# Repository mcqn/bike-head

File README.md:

# Bike Head

Making your bike more fun (if that's possible) by giving it a head.

A laser-cut template to make a cardboard head to mount on the handlebars of your bike.  Then customize it with craft supplies or LEDs and a Microbit.

## Notes on creating the design

In FreeCAD...

1. Created a sketch of the side profile
1. Made a copy of that sketch
1. Opened the attachment editor for each sketch and offset one by 75mm on Z and -8&deg; rotation around Y, and the other by -75 and 8&deg;
1. Then in the Surface workbench, filled in each side to give two surfaces
1. And then repeatedly used the boundary curve to create each connecting surface between the sides
1. In the Draft workbench I selected all the centre, connecting surfaces and upgraded them to a shell
1. Then in the Mesh workbench I could convert the shell to a mesh and then unwrap it to get the net for those shapes
1. The convert to mesh and unwrap process was repeated for the two sides
1. Then used Transform to orient the sides to broadly the right place
1. And in the Draft workbench rotated and moved the sides to be offset by 3mm from the long face
   1. Selected each end of the corresponding lines in the side and the centre piece which are to be lined up, and noted their `x` and `y` coordinates.
   1. Worked out the angle of the centre piece line with respect to `y` (in this instance) - `theta`, with `tan^-1(x_diff/y_diff)`
   1. Worked out new coordinates for corresponding point in the side with `x_offset` being `3 * sin(90-theta)` and `y_offset` being `3* cos(90-theta)`
   1. Work out the distance to move the side so it ends up at the right place.  Use the Placement in the side's properties to nudge it
   1. Rotate the side to line up parallel to the corresponding line in the centre.  I ended up eyeballing this rather than calculating it
   1. Repeat for the other side

## Game Notes

### Pacman

### Tick

1. Start up and loop until someone is chosen or a timeout happens:
   1. Transmit your ID
   1. Wait to receive someone-else's ID
   1. Vote on who should be `it`?
1. If it was a timeout, assume someone else is `it` and proceed

1. To begin with, use a button press to select someone as `it`
1. Loop:
   1. If I'm `it`:
      1. Light LED
      1. Broadcast our ID
      1. Listen for a broadcast
      1. If a request to be `it` is received, send a confirmation of passing on
   1. If not `it`:
      1. Turn off LED
      1. Listen for a broadcast
      1. If one found, reply with a request to be `it`
      1. If it's a confirmation of `it`, you're `it`, count down from 5 before looping round

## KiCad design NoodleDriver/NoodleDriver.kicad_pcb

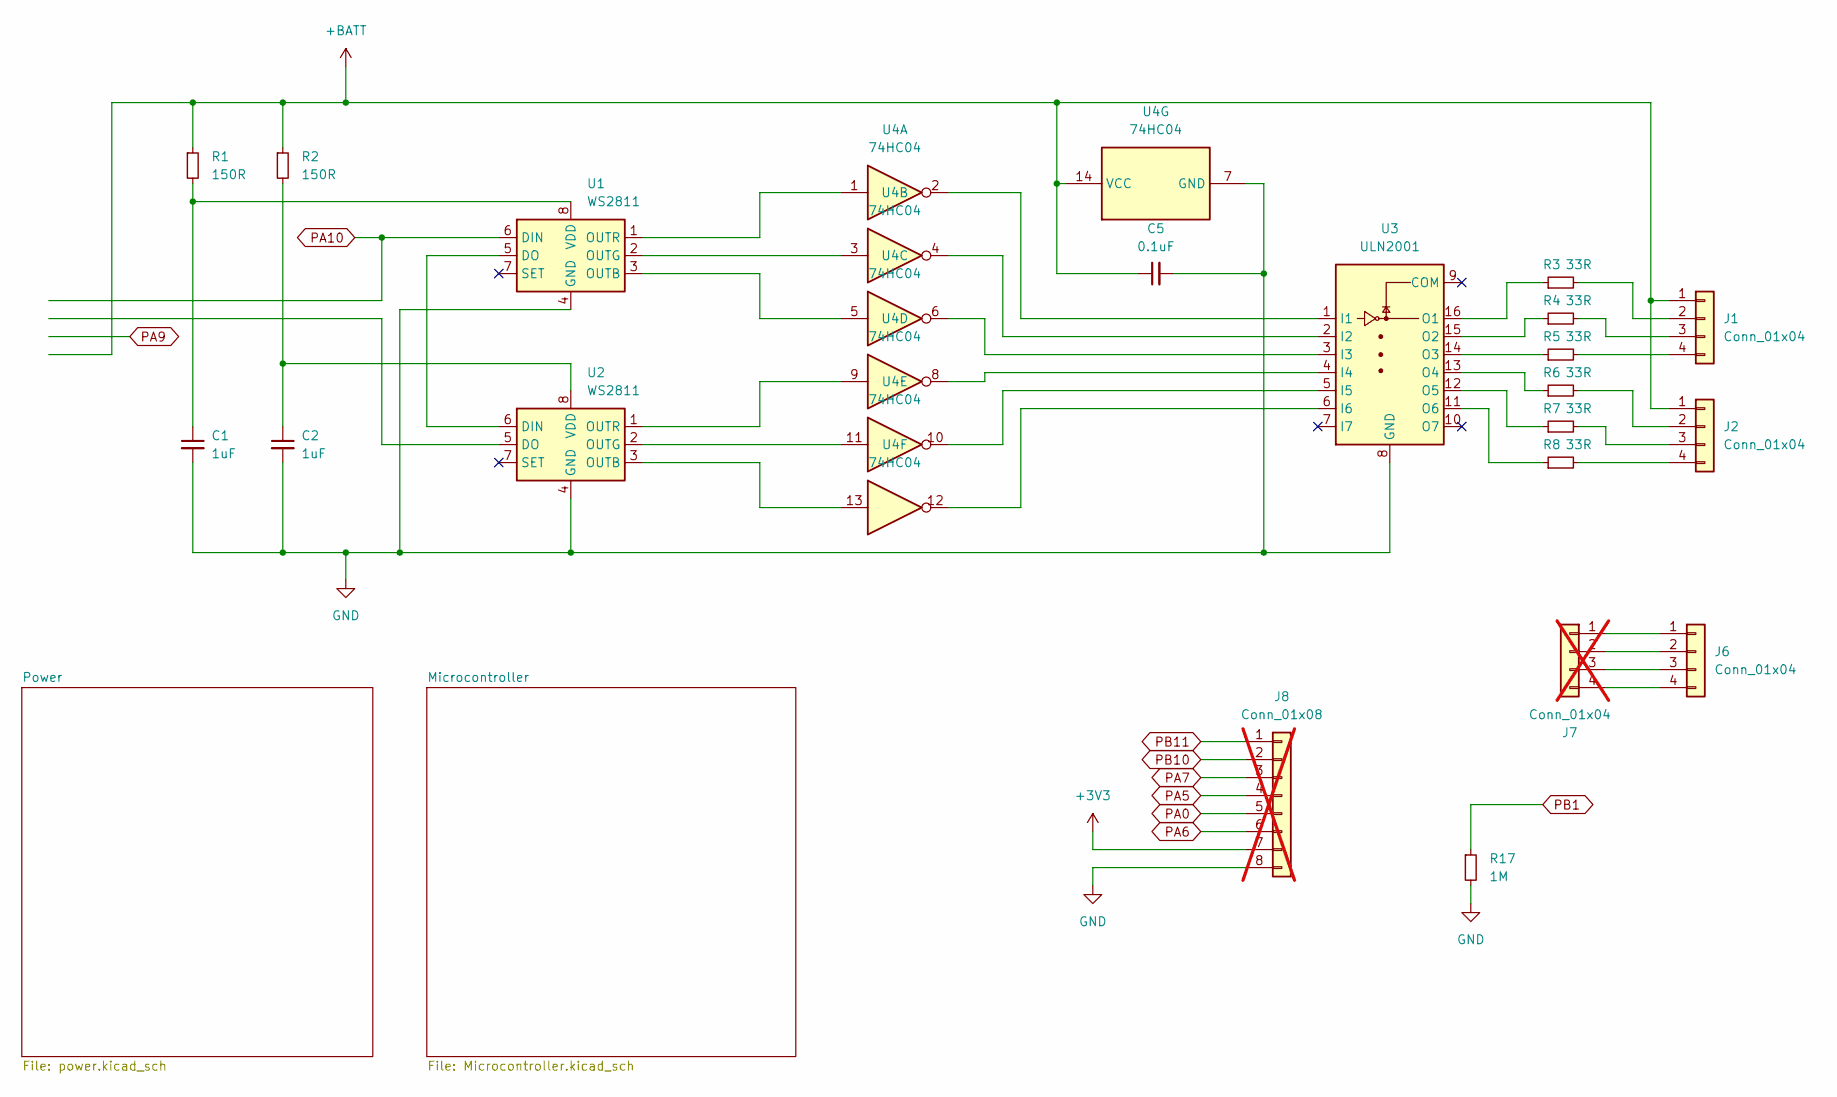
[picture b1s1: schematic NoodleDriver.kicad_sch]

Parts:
C1, C2: 1uF; C_0402_1005Metric; LCSC C14445
C5: 0.1uF; C_0402_1005Metric; LCSC C77020
J1, J2, J6: Conn_01x04; MagneticPogoPinConnector_1x04_P2.54mm_Horizontal
J7: Conn_01x04; PinSocket_1x04_P2.54mm_Vertical; not fitted
J8: Conn_01x08; PinSocket_1x08_P2.54mm_Vertical; not fitted
R1, R2: 150R; R_0402_1005Metric; LCSC C138054
R3, R4, R5, R6, R7, R8: 33R; R_0603_1608Metric
R17: 1M; R_0402_1005Metric
U1, U2: WS2811; SOP-8_3.76x4.96mm_P1.27mm; LCSC C114581
U3: ULN2001; SOIC-16_3.9x9.9mm_P1.27mm; LCSC C165966
U4: 74HC04; SOIC-14_3.9x8.7mm_P1.27mm; LCSC C86613

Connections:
+3V3: J8.7; also elsewhere on the board
+BATT: C5.1, J1.1, J2.1, R1.1, R2.1, U4.14 (VCC); also elsewhere on the board
GND: C1.2, C2.2, C5.2, J8.8, R17.2, U1.4 (GND), U2.4 (GND), U3.8 (GND), U4.7 (GND); also elsewhere on the board
unnamed: J1.2, R3.2
unnamed: J1.3, R4.2
unnamed: J1.4, R5.2
unnamed: J2.2, R6.2
unnamed: J2.3, R7.2
unnamed: J2.4, R8.2
unnamed: J6.1, J7.1
unnamed: J6.2, J7.2
unnamed: J6.3, J7.3
unnamed: J6.4, J7.4
unnamed: U1.5 (DO), U2.6 (DIN)
unnamed: U1.3 (OUTB), U4.5
unnamed: U1.2 (OUTG), U4.3
unnamed: U1.1 (OUTR), U4.1
unnamed: C1.1, R1.2, U1.8 (VDD)
unnamed: U2.3 (OUTB), U4.13
unnamed: U2.2 (OUTG), U4.11
unnamed: U2.1 (OUTR), U4.9
unnamed: C2.1, R2.2, U2.8 (VDD)
unnamed: U3.1 (I1), U4.2
unnamed: U3.2 (I2), U4.4
unnamed: U3.3 (I3), U4.6
unnamed: U3.4 (I4), U4.8
unnamed: U3.5 (I5), U4.10
unnamed: U3.6 (I6), U4.12
unnamed: R3.1, U3.16 (O1)
unnamed: R4.1, U3.15 (O2)
unnamed: R5.1, U3.14 (O3)
unnamed: R6.1, U3.13 (O4)
unnamed: R7.1, U3.12 (O5)
unnamed: R8.1, U3.11 (O6)
PA0: J8.5; also elsewhere on the board
PA5: J8.4; also elsewhere on the board
PA6: J8.6; also elsewhere on the board
PA7: J8.3; also elsewhere on the board
PA10: U1.6 (DIN); also elsewhere on the board
PB1: R17.1; also elsewhere on the board
PB10: J8.2; also elsewhere on the board
PB11: J8.1; also elsewhere on the board

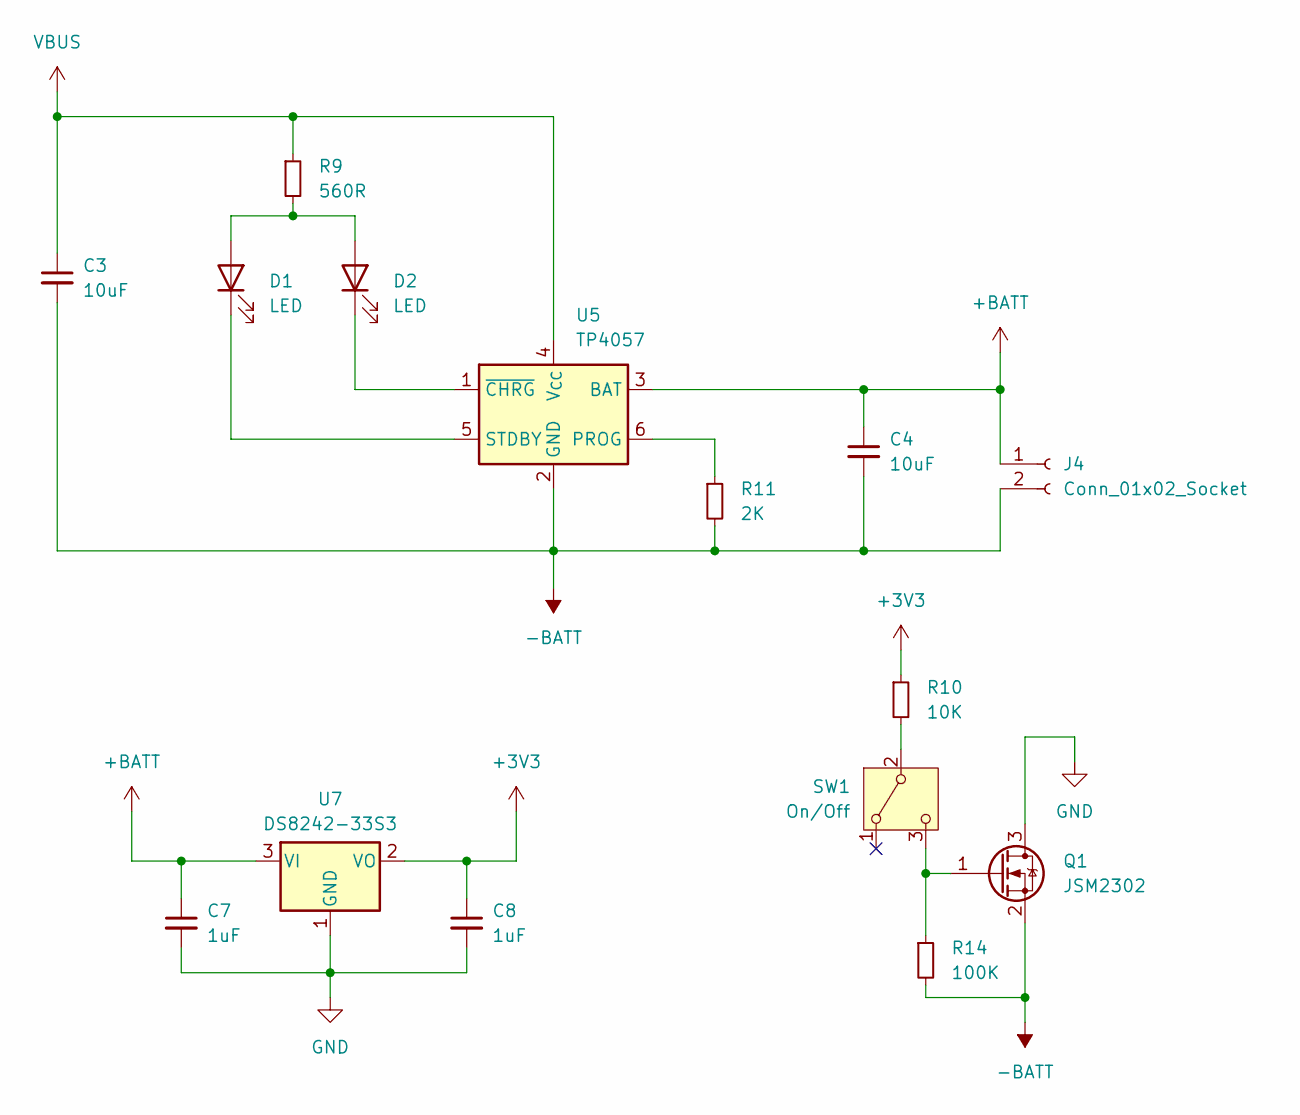
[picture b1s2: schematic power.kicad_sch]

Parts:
C3, C4: 10uF; C_0603_1608Metric; LCSC C6119842
C7, C8: 1uF; C_0402_1005Metric; LCSC C14445
D1, D2: LED; LED_0402_1005Metric
J4: Conn_01x02_Socket; JST_PH_B2B-PH-SM4-TB_1x02-1MP_P2.00mm_Vertical
Q1: JSM2302; SOT-23; LCSC C916403
R9: 560R; R_0402_1005Metric; LCSC C163460
R10: 10K; R_0402_1005Metric
R11: 2K; R_0402_1005Metric; LCSC C4109
R14: 100K; R_0402_1005Metric
SW1: On/Off; SW_Slide_SPDT_Angled_CK_OS102011MA1Q; Farnell 1201431
U5: TP4057; TSOT-23-6; LCSC C725791
U7: DS8242-33S3; SOT-23-3; LCSC C5884132

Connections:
+3V3: C8.1, R10.1, U7.2 (VO); also elsewhere on the board
+BATT: C4.1, C7.1, J4.1, U5.3 (BAT), U7.3 (VI); also elsewhere on the board
-BATT: C3.2, C4.2, J4.2, Q1.2 (S), R11.2, R14.2, U5.2 (GND); also elsewhere on the board
GND: C7.2, C8.2, Q1.3 (D), U7.1 (GND); also elsewhere on the board
unnamed: D1.2 (A), D2.2 (A), R9.2
unnamed: D1.1 (K), U5.5 (STDBY)
unnamed: D2.1 (K), U5.1 (~CHRG)
unnamed: Q1.1 (G), R14.1, SW1.3 (C)
unnamed: R10.2, SW1.2 (B)
unnamed: R11.1, U5.6 (PROG)
VBUS: C3.1, R9.1, U5.4 (V_{CC}); also elsewhere on the board

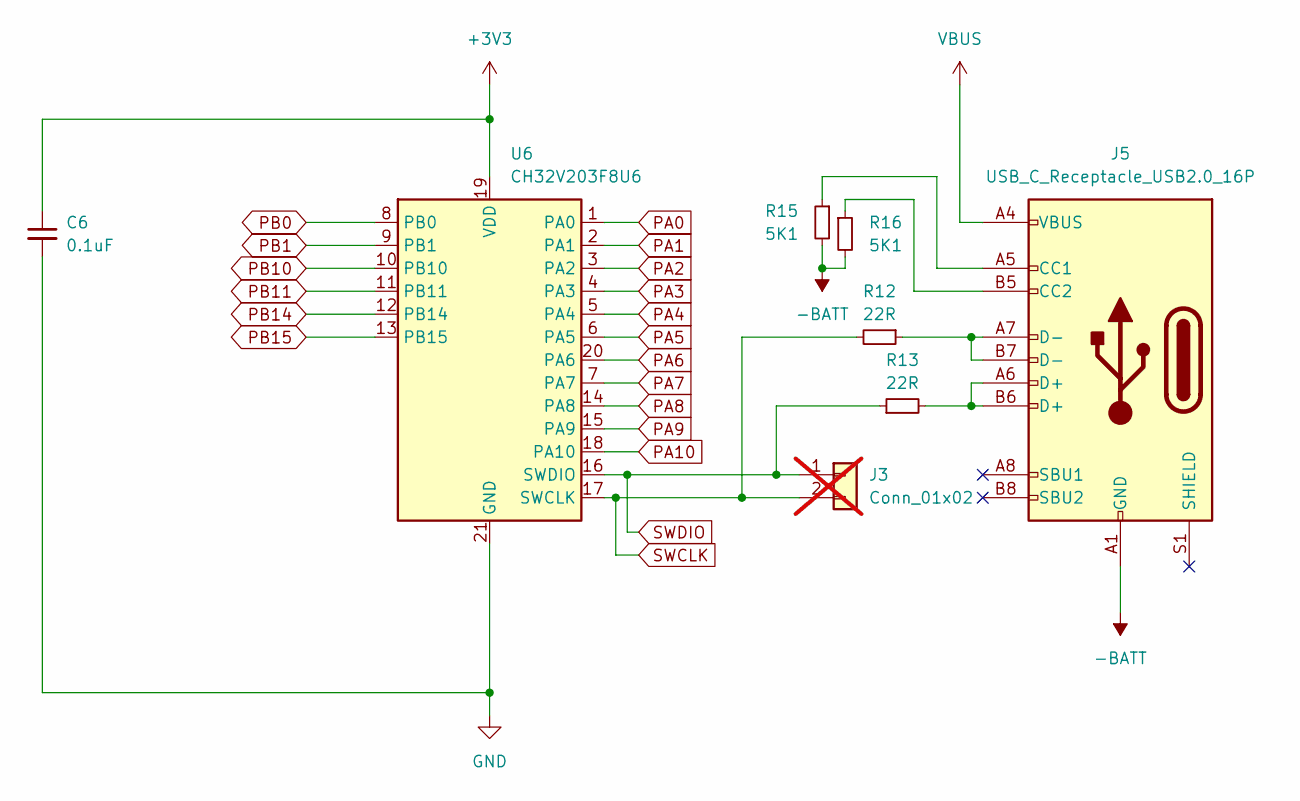
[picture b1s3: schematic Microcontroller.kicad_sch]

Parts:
C6: 0.1uF; C_0402_1005Metric; LCSC C77020
J3: Conn_01x02; PinSocket_1x02_P2.54mm_Vertical; not fitted
J5: USB_C_Receptacle_USB2.0_16P; USB_C_PADDLE
R12, R13: 22R; R_0402_1005Metric; LCSC C114765
R15, R16: 5K1; R_0402_1005Metric; LCSC C25905
U6: CH32V203F8U6; QFN-20-1EP_3x3mm_P0.45mm_EP1.6x1.6mm; LCSC C7570477

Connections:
+3V3: C6.1, U6.19 (VDD); also elsewhere on the board
-BATT: J5.A1 (GND), J5.A12 (GND), J5.B1 (GND), J5.B12 (GND), R15.2, R16.2; also elsewhere on the board
GND: C6.2, U6.21 (GND); also elsewhere on the board
unnamed: J5.A5 (CC1), R15.1
unnamed: J5.B5 (CC2), R16.1
unnamed: J5.A6 (D+), J5.B6 (D+), R13.2
unnamed: J5.A7 (D-), J5.B7 (D-), R12.1
PA0: U6.1 (PA0); also elsewhere on the board
PA1: U6.2 (PA1)
PA2: U6.3 (PA2)
PA3: U6.4 (PA3)
PA4: U6.5 (PA4)
PA5: U6.6 (PA5); also elsewhere on the board
PA6: U6.20 (PA6); also elsewhere on the board
PA7: U6.7 (PA7); also elsewhere on the board
PA8: U6.14 (PA8)
PA9: U6.15 (PA9)
PA10: U6.18 (PA10); also elsewhere on the board
PB0: U6.8 (PB0)
PB1: U6.9 (PB1); also elsewhere on the board
PB10: U6.10 (PB10); also elsewhere on the board
PB11: U6.11 (PB11); also elsewhere on the board
PB14: U6.12 (PB14)
PB15: U6.13 (PB15)
SWCLK: J3.2, R12.2, U6.17 (SWCLK)
SWDIO: J3.1, R13.1, U6.16 (SWDIO)
VBUS: J5.A4 (VBUS), J5.A9 (VBUS), J5.B4 (VBUS), J5.B9 (VBUS); also elsewhere on the board

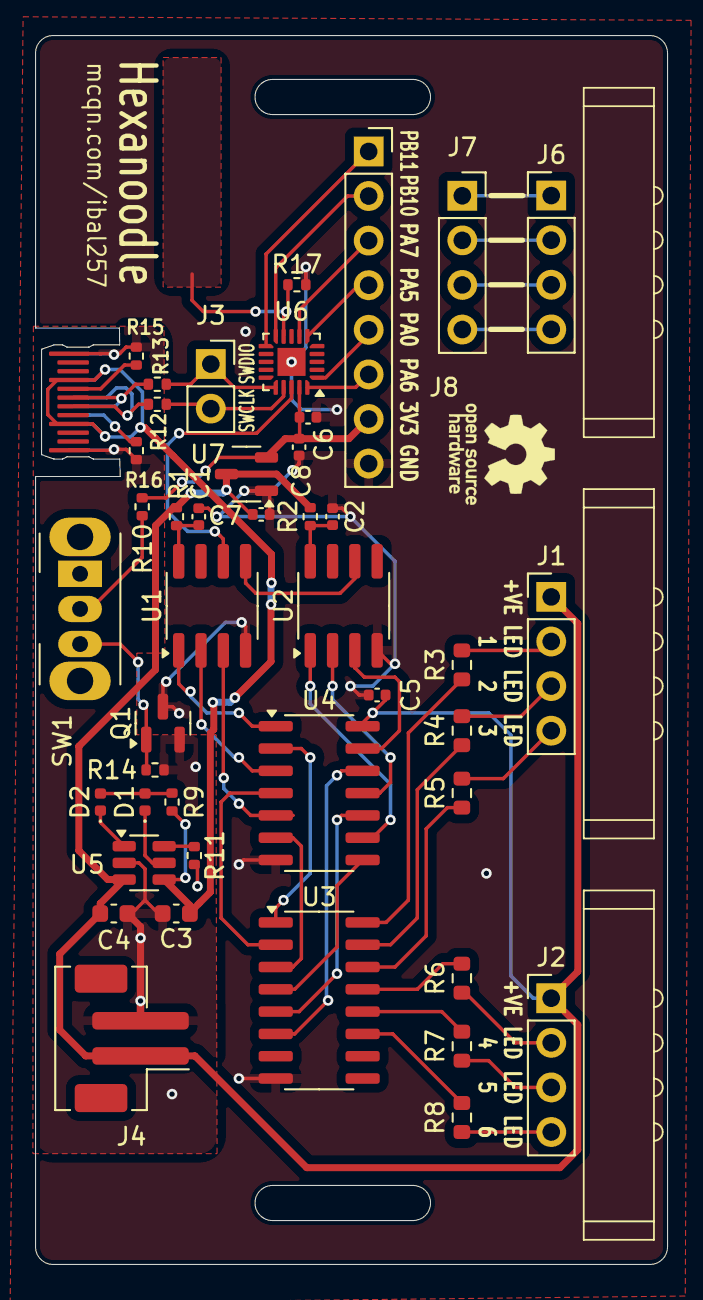
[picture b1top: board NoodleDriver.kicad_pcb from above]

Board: 2 copper layers, 36.0 x 70.0 mm, 44 parts (0 on the bottom side), 56 nets.

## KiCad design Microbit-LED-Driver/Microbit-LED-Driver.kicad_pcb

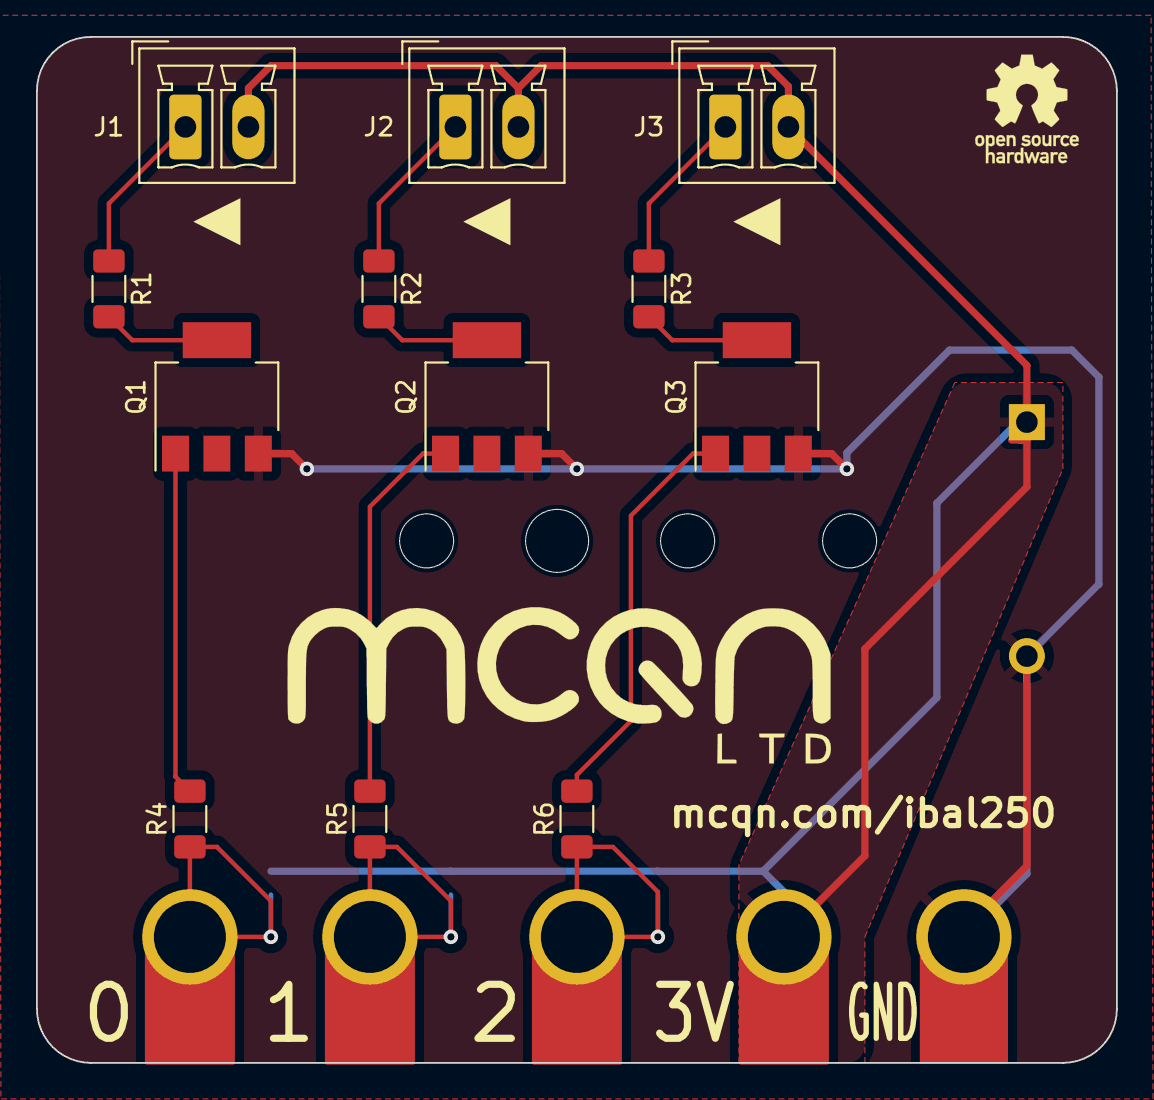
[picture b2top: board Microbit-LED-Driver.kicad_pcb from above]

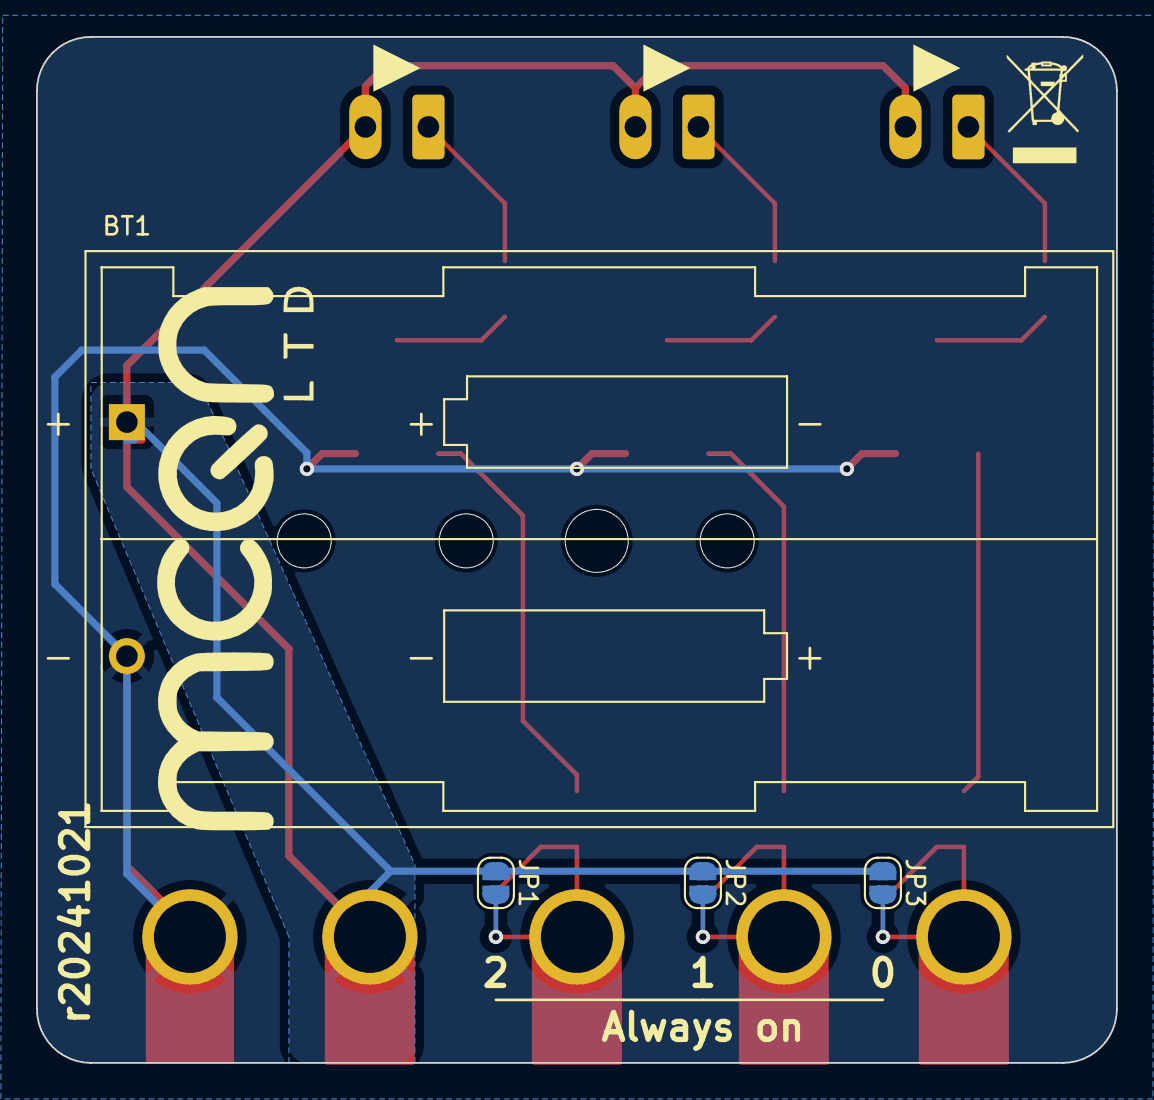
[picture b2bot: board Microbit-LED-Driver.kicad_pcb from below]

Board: 2 copper layers, 60.0 x 57.0 mm, 17 parts (4 on the bottom side), 14 nets.

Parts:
BT1: Battery; BatteryHolder_Multicomp_MP000325_2xAA
J1, J2, J3: Conn_01x02_Socket; PhoenixContact_MCV_1,5_2-G-3.5_1x02_P3.50mm_Vertical
J4: Microbit Bolt Connector
JP1, JP2, JP3: SolderJumper_2_Open; SolderJumper-2_P1.3mm_Open_RoundedPad1.0x1.5mm
Q1, Q2, Q3: BCP56; SOT-223-3_TabPin2
R1, R2, R3, R4, R5, R6: R_Small; R_1206_3216Metric_Pad1.30x1.75mm_HandSolder

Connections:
+3V0: BT1.1 (+), J1.2, J2.2, J3.2, J4.3 (3V), JP1.1 (A), JP2.1 (A), JP3.1 (A)
GND: BT1.2 (-), J4.4 (GND), Q1.3 (E), Q2.3 (E), Q3.3 (E)
unnamed: J1.1, R1.1
unnamed: J2.1, R2.1
unnamed: J3.1, R3.1
unnamed: J4.2, JP1.2 (B), R6.1
unnamed: J4.1, JP2.2 (B), R5.1
unnamed: J4.0, JP3.2 (B), R4.1
unnamed: Q1.1 (B), R4.2
unnamed: Q1.2 (C), R1.2
unnamed: Q2.1 (B), R5.2
unnamed: Q2.2 (C), R2.2
unnamed: Q3.1 (B), R6.2
unnamed: Q3.2 (C), R3.2

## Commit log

2024-08-26 Initial version for testing, and adding the licence.
2024-08-26 Add tabs and more fold lines.
2024-09-16 First pass of LED driver PCB, as sent for fabbing. Part of #2
2024-10-09 Make a start on parts required for a full kit.
2024-10-09 Fix markdown for the table.
2024-10-21 Nugde position of screw terminals and battery holder so they shouldn't clash. Fixes #3
2025-08-21 First sketch of design using WS2811 drivers to drive more noodles. Part of #8
2025-09-17 Add a microcontroller, and regulator and USB-C connector. Checkin before I try swapping out the microbit and 0.1" headers. Part of #8
2025-09-24 Exclude the USB contacts from the solderpaste layers.
2025-10-05 Final tuning of prototype board, which we've ordered a handful of prototypes to be fabbed. Part of #8
